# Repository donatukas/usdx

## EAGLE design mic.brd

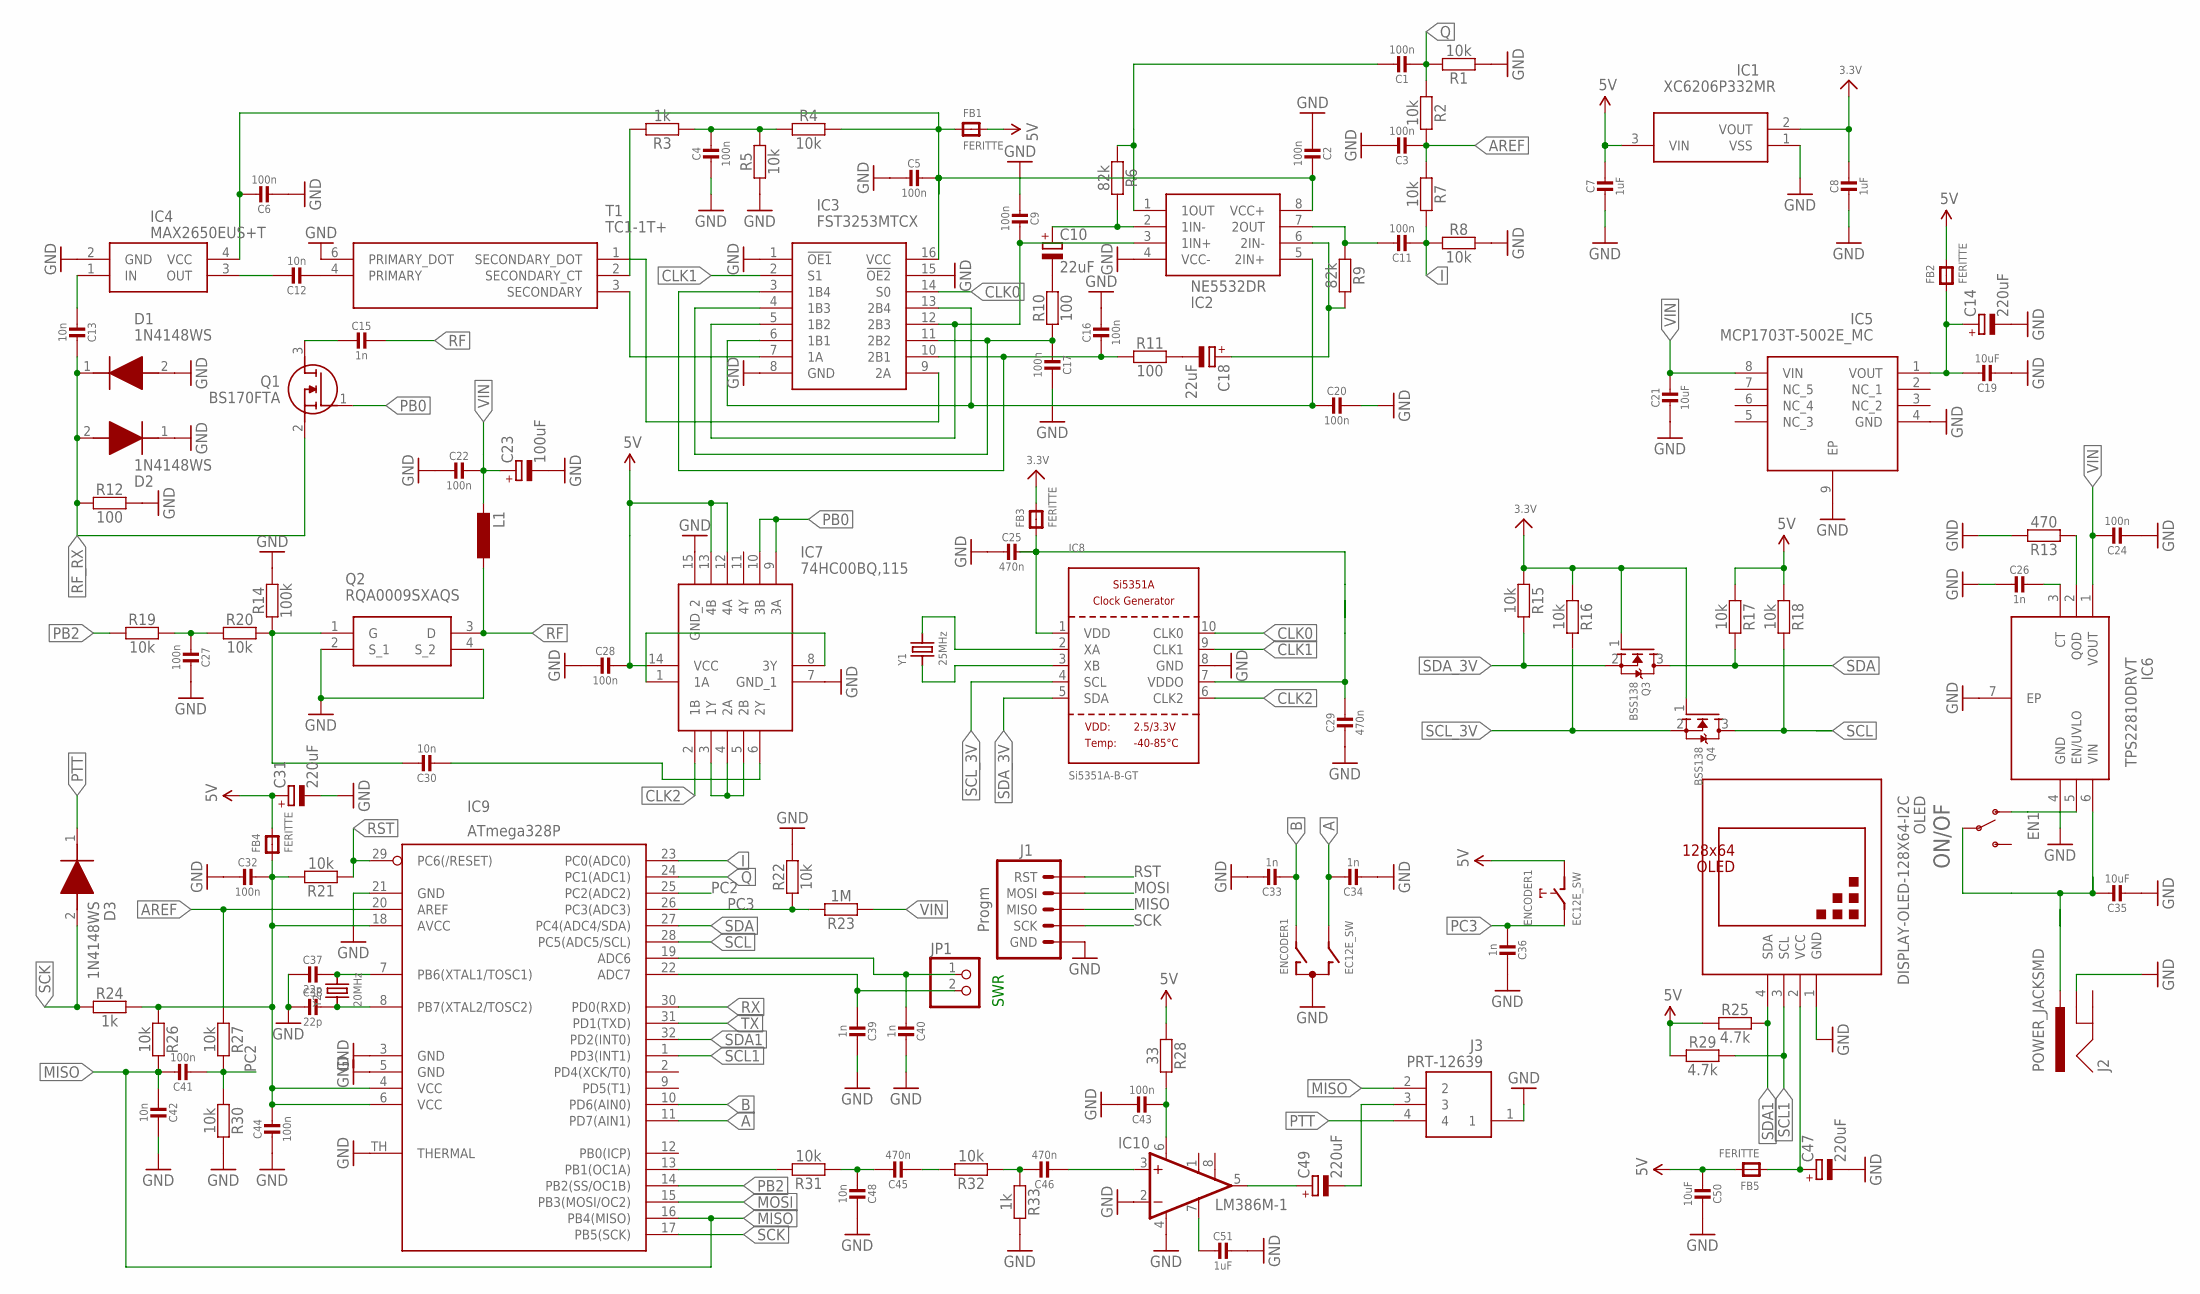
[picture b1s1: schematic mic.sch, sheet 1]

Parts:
C1, C2, C3, C4, C5, C6, C9, C11, C16, C17, C20, C22, C27, C28, C32, C41, C43, C44: 100n; _0402
C7, C8: 1uF; _0603
C10, C18: 22uF; SMC_A
C12, C13, C30, C42, C48: 10n; _0402
C14, C31, C47, C49: 220uF; SANYO-OSCON_A
C15: 1n; _0603
C19, C21, C50: 10uF; _0402
C23: 100uF; SMC_D
C24: 100n; _0805
C25, C29, C45, C46: 470n; _0402
C26, C33, C34, C36, C39, C40: 1n; _0402
C35: 10uF; _0805
C37, C38: 22p; _0402
C51: 1uF; _0402
D1: 1N4148WS; SODFL2512X90N
D2, D3: 1N4148WS; SODFL2512X90N; MANUFACTURER_PART_NUMBER 1N4148WS; MOUSER_PART_NUMBER 512-1N4148WS
ENCODER1: EC12E_SW; ALPS_EC12E_SW; MPN EC12E2424407
FB1, FB2, FB3, FB4, FB5: FERITTE; _0603
IC1: XC6206P332MR; SOT95P280X130-3N
IC2: NE5532DR; SOIC127P600X175-8N
IC3: FST3253MTCX; SOP65P640X110-16N
IC4: MAX2650EUS+T; 4-SOT143
IC5: MCP1703T-5002E_MC; SON50P300X200X100-9N
IC6: TPS22810DRVT; SON65P200X200X80-7N
IC7: 74HC00BQ,115; 74HC00BQ115
IC8: Si5351A-B-GT; MSOP10
IC9: ATmega328P; MLF32-TH
IC10: LM386M-1; SO08
J1: Progm; SPARKFUN-CONNECTORS_PIC-ICSP-MINI
J2: POWER_JACKSMD; POWER_JACK_SMD
J3: PRT-12639; PRT12639
JP1: PINHD-1X2; 1X02
L1: RCL_L-EUTFI0305; RCL_TFI0305
OLED: DISPLAY-OLED-128X64-I2C; NEW_DIY-MODULES_(1)_DISPLAY-OLED-128X64-I2C
ON/OF: SWITCH-SPDT-SMD-RIGHT-ANGLE; SWITCH_SPST_SMD_A
Q1: BS170FTA; SOT96P240X100-3N
Q2: RQA0009SXAQS
Q3, Q4: BSS138; SOT23-WIDE
R1, R2, R4, R5, R7, R8, R15, R16, R17, R18, R19, R20, R21, R22, R26, R27, R30, R31, R32: 10k; C0402
R3, R24, R33: 1k; C0402
R6, R9: 82k; C0402
R10, R11: 100; C0402
R12: 100; C0603
R13: 470; C0402
R14: 100k; C0402
R23: 1M; C0402
R25, R29: 4.7k; C0402
R28: 33; C0805
T1: TC1-1T+; TC11T
Y1: 25MHz; CRYSTAL_3.2X2.5
Y2: 20MHz; CRYSTAL_3.2X2.5

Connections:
5V: C7.1, C28.1, C31.+, C50.2, ENCODER1.D (1), FB1.2, FB2.2, FB4.2, FB5.2, IC1.3 (VIN), IC7.12 (4A), IC7.13 (4B), IC7.14 (VCC), R17.2, R18.2, R25.2, R28.2, R29.2; also elsewhere on the board
A: C34.1, ENCODER1.B, IC9.11 (PD7(AIN1))
AREF: C3.2, IC9.20 (AREF), R2.1, R7.2, R27.2
B: C33.2, ENCODER1.A, IC9.10 (PD6(AIN0))
CLK0: IC3.14 (S0), IC8.10 (CLK0)
CLK1: IC3.2 (S1), IC8.9 (CLK1)
CLK2: IC7.2 (1B), IC8.6 (CLK2)
EN1: IC6.5 (EN/UVLO), ON/OF.1 (O)
GND: C2.2, C3.1, C4.2, C5.2, C6.2, C7.2, C8.2, C9.2, C14.-, C16.1, C17.1, C19.2, C20.1, C21.2, C22.2, C23.-, C24.2, C25.2, C26.2, C27.1, C28.2, C29.2, C31.-, C32.2, C33.1, C34.2, C35.2, C36.1, C37.2, C38.2, C39.1, C40.1, C42.1, C43.1, C44.2, C47.-, C48.1, C50.1, C51.1, D1.2 (A), D2.1 (K), ENCODER1.C, IC1.1 (VSS), IC2.4 (VCC-), IC3.1 (!OE1), IC3.8 (GND), IC3.15 (!OE2), IC4.2 (GND), IC5.4 (GND), IC5.9 (EP), IC6.4 (GND), IC6.7 (EP), IC7.7 (GND_1), IC7.15 (GND_2), IC8.8 (GND), IC9.3 (GND), IC9.5 (GND), IC9.21 (GND), IC9.TH (THERMAL), IC10.2 (-IN), IC10.4 (GND), J1.5 (GND), J2.GND (GNDBREAK), J3.1, OLED.1 (GND), Q2.2 (S_1), Q2.4 (S_2), R1.2, R5.2, R8.1, R12.1, R13.2, R14.1, R22.1, R30.1, R33.1, T1.6 (PRIMARY_DOT); also elsewhere on the board
I: C11.2, IC9.23 (PC0(ADC0)), R7.1, R8.2
MISO: C41.1, C42.2, IC9.16 (PB4(MISO)), J1.3 (MISO), J3.2, R26.1
MOSI: IC9.15 (PB3(MOSI/OC2)), J1.2 (MOSI)
unnamed: IC7.3 (1Y), IC7.4 (2A), IC7.5 (2B)
unnamed: IC3.7 (1A), T1.3 (SECONDARY)
unnamed: C47.+, FB5.1, OLED.2 (VCC)
unnamed: C37.1, IC9.7 (PB6(XTAL1/TOSC1)), Y2.2
unnamed: C38.1, IC9.8 (PB7(XTAL2/TOSC2)), Y2.1
unnamed: IC3.9 (2A), T1.1 (SECONDARY_DOT)
unnamed: C4.1, R3.2, R4.2, R5.1
unnamed: IC7.1 (1A), IC7.8 (3Y)
unnamed: C30.2, IC7.6 (2Y)
unnamed: C30.1, Q2.1 (G), R14.2, R20.1
unnamed: C27.2, R19.1, R20.2
unnamed: C26.1, IC6.3 (CT)
unnamed: C20.2, IC2.5 (2IN+), IC3.6 (1B1), IC3.13 (2B4)
unnamed: C9.1, IC2.3 (1IN+), IC3.5 (1B2), IC3.12 (2B3)
unnamed: R3.1, T1.2 (SECONDARY_CT)
unnamed: C17.2, IC3.4 (1B3), IC3.11 (2B2), R10.2
unnamed: C16.2, IC3.3 (1B4), IC3.10 (2B1), R11.2
unnamed: C1.1, IC2.1 (1OUT), R6.2
unnamed: IC9.13 (PB1(OC1A)), R31.1
unnamed: C45.1, C48.2, R31.2
unnamed: C11.1, IC2.7 (2OUT), R9.2
unnamed: C18.-, R11.1
unnamed: C18.+, IC2.6 (2IN-), R9.1
unnamed: C10.+, IC2.2 (1IN-), R6.1
unnamed: C10.-, R10.1
unnamed: C45.2, R32.1
unnamed: C46.1, R32.2, R33.2
unnamed: C32.1, C44.1, FB4.1, IC9.4 (VCC), IC9.6 (VCC), IC9.18 (AVCC), R21.1, R24.1, R26.2
unnamed: C46.2, IC10.3 (+IN)
unnamed: C43.2, IC10.6 (VS), R28.1
unnamed: C51.2, IC10.7 (BYPASS)
unnamed: C49.+, IC10.5 (OUT)
unnamed: C49.-, J3.3
unnamed: C12.2, T1.4 (PRIMARY)
unnamed: C12.1, IC4.3 (OUT)
unnamed: C13.2, IC4.1 (IN)
unnamed: C15.2, Q1.3 (D)
unnamed: C14.+, C19.1, FB2.1, IC5.1 (VOUT)
unnamed: C2.1, C5.1, C6.1, FB1.1, IC2.8 (VCC+), IC3.16 (VCC), IC4.4 (VCC), R4.1
unnamed: IC8.3 (XB), Y1.1
unnamed: IC8.2 (XA), Y1.2
unnamed: IC6.2 (QOD), R13.1
unnamed: C25.1, C29.1, FB3.1, IC8.1 (VDD), IC8.7 (VDDO)
unnamed: C40.2, IC9.19 (ADC6), JP1.1
unnamed: C39.2, IC9.22 (ADC7), JP1.2
PB0: IC7.9 (3A), IC7.10 (3B), Q1.1 (G)
PB2: IC9.14 (PB2(SS/OC1B)), R19.2
PC2: C41.2, IC9.25 (PC2(ADC2)), R27.1, R30.2
PC3: C36.2, ENCODER1.E (2), IC9.26 (PC3(ADC3)), R22.2, R23.1
PTT: D3.1 (K), J3.4
Q: C1.2, IC9.24 (PC1(ADC1)), R1.1, R2.2
RF: C15.1, L1.1, Q2.3 (D); also elsewhere on the board
RF_RX: C13.1, D1.1 (K), D2.2 (A), Q1.2 (S), R12.2
RST: IC9.29 (PC6(/RESET)), J1.1 (RST), R21.2
RX: IC9.30 (PD0(RXD)); also elsewhere on the board
SCK: D3.2 (A), IC9.17 (PB5(SCK)), J1.4 (SCK), R24.2
SCL: IC9.28 (PC5(ADC5/SCL)), Q4.3 (D), R18.1; also elsewhere on the board
SCL1: IC9.1 (PD3(INT1)), OLED.3 (SCL), R29.1
SCL_3V: IC8.4 (SCL), Q4.2 (S), R16.1
SDA: IC9.27 (PC4(ADC4/SDA)), Q3.3 (D), R17.1; also elsewhere on the board
SDA1: IC9.32 (PD2(INT0)), OLED.4 (SDA), R25.1
SDA_3V: IC8.5 (SDA), Q3.2 (S), R15.1
TX: IC9.31 (PD1(TXD)); also elsewhere on the board
VDD: C8.1, FB3.2, IC1.2 (VOUT), Q3.1 (G), Q4.1 (G), R15.2, R16.2
VIN: C21.1, C22.1, C23.+, C24.1, IC5.8 (VIN), IC6.1 (VOUT), L1.2, R23.2
VIN1: C35.1, IC6.6 (VIN), J2.VIN0 (PWR), ON/OF.2

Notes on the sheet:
SWR

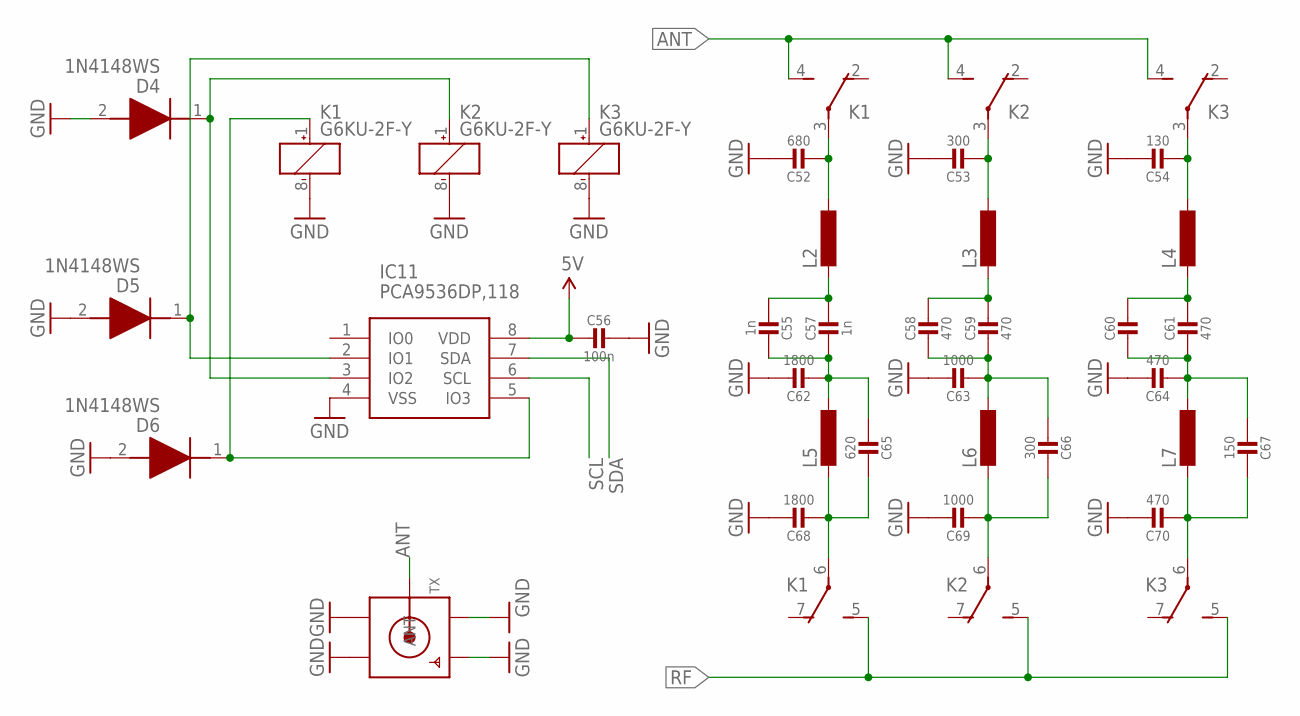
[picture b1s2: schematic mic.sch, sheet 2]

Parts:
C52: 680; _0603
C53, C66: 300; _0603
C54: 130; _0603
C55, C57: 1n; _0603
C56: 100n; _0402
C58, C59, C61, C64, C70: 470; _0603
C60: CAP_CERAMIC_0603; _0603
C62, C68: 1800; _0603
C63, C69: 1000; _0603
C65: 620; _0603
C67: 150; _0603
D4, D5: 1N4148WS; SODFL2512X90N; MANUFACTURER_PART_NUMBER 1N4148WS; MOUSER_PART_NUMBER 512-1N4148WS
D6: 1N4148WS; SODFL2512X90N
IC11: PCA9536DP,118; SOP65P490X110-8N
K1: G6KU-2F-Y
K2, K3: G6KU-2F-Y; MPN G6KU-2F-Y DC3
L2, L3, L4, L5, L6, L7: RCL_L-EUTFI0305; RCL_TFI0305
TX: MODULATOR_MICROBUILDER_SMACONNECTOR_EDGE_UFL; MODULATOR_MICROBUILDER_SMA_EDGELAUNCH_UFL

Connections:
5V: C56.2, IC11.8 (VDD); also elsewhere on the board
ANT: K1.4 (S), K2.4 (S), K3.4 (S), TX.P (ANT)
GND: C52.1, C53.1, C54.1, C56.1, C62.1, C63.1, C64.1, C68.1, C69.1, C70.1, D4.2 (A), D5.2 (A), D6.2 (A), IC11.4 (VSS), K1.8 (-), K2.8 (-), K3.8 (-), TX.GND@1 (GND1), TX.GND@2 (GND2), TX.GND@3 (GND3), TX.GND@4 (GND4); also elsewhere on the board
unnamed: C55.2, C57.1, L2.2
unnamed: C55.1, C57.2, C62.2, C65.2, L5.1
unnamed: C58.1, C59.1, L3.2
unnamed: C52.2, K1.3, L2.1
unnamed: C53.2, K2.3, L3.1
unnamed: C54.2, K3.3, L4.1
unnamed: C67.1, C70.2, K3.6, L7.2
unnamed: C66.1, C69.2, K2.6, L6.2
unnamed: C65.1, C68.2, K1.6, L5.2
unnamed: C58.2, C59.2, C63.2, C66.2, L6.1
unnamed: C60.2, C61.2, C64.2, C67.2, L7.1
unnamed: C60.1, C61.1, L4.2
unnamed: D6.1 (K), IC11.5 (IO3), K1.1 (+)
unnamed: D4.1 (K), IC11.3 (IO2), K2.1 (+)
unnamed: D5.1 (K), IC11.2 (IO1), K3.1 (+)
RF: K1.5 (S), K2.5 (S), K3.5 (S); also elsewhere on the board
SCL: IC11.6 (SCL); also elsewhere on the board
SDA: IC11.7 (SDA); also elsewhere on the board

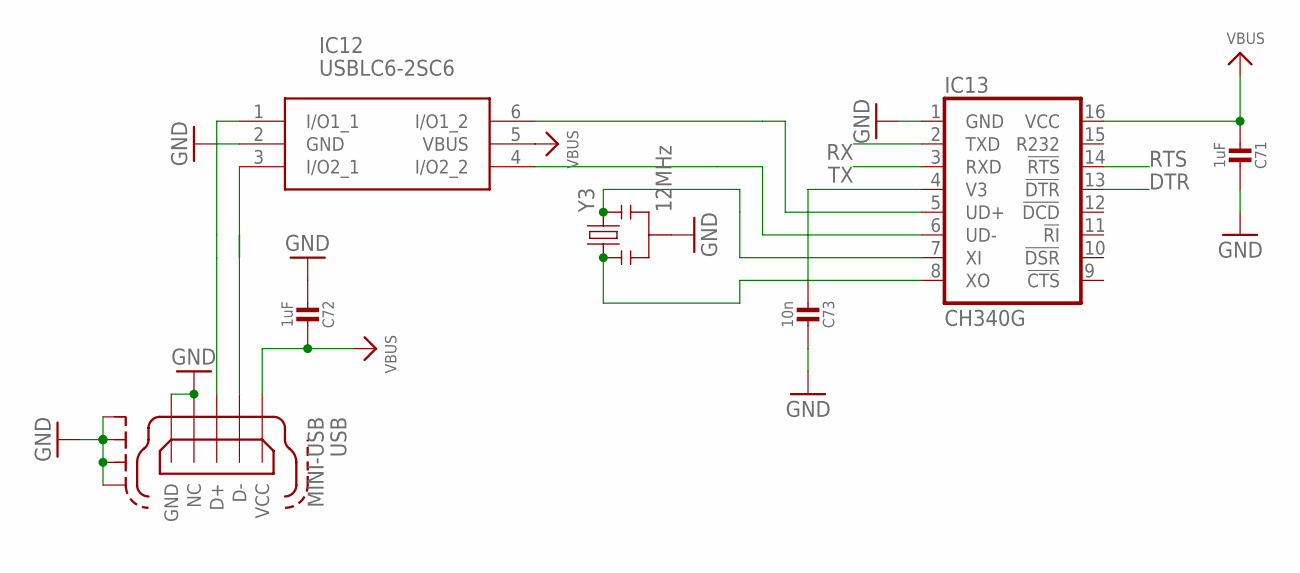
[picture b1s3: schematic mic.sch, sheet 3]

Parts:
C71, C72: 1uF; _0603
C73: 10n; _0603
IC12: USBLC6-2SC6; SOT95P280X145-6N
IC13: CH340G; SO016
USB: MINI-USB; MINI-USB-B5
Y3: 12MHz; RESONATOR-SMD

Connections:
DTR: IC13.13 (!DTR)
GND: C71.1, C72.2, C73.1, IC12.2 (GND), IC13.1 (GND), USB.4 (NC), USB.5 (GND), USB.M1 (S1), USB.M2 (S2), USB.M3 (S3), USB.M4 (S4), Y3.2; also elsewhere on the board
unnamed: IC12.6 (I/O1_2), IC13.5 (UD+)
unnamed: IC12.4 (I/O2_2), IC13.6 (UD-)
unnamed: IC13.8 (XO), Y3.1
unnamed: IC13.7 (XI), Y3.3
unnamed: IC12.1 (I/O1_1), USB.3 (D+)
unnamed: IC12.3 (I/O2_1), USB.2 (D-)
RTS: IC13.14 (!RTS)
RX: IC13.2 (TXD); also elsewhere on the board
TX: IC13.3 (RXD); also elsewhere on the board
V3: C73.2, IC13.4 (V3)
VBUS: C71.2, C72.1, IC12.5 (VBUS), IC13.16 (VCC), USB.1 (VCC)

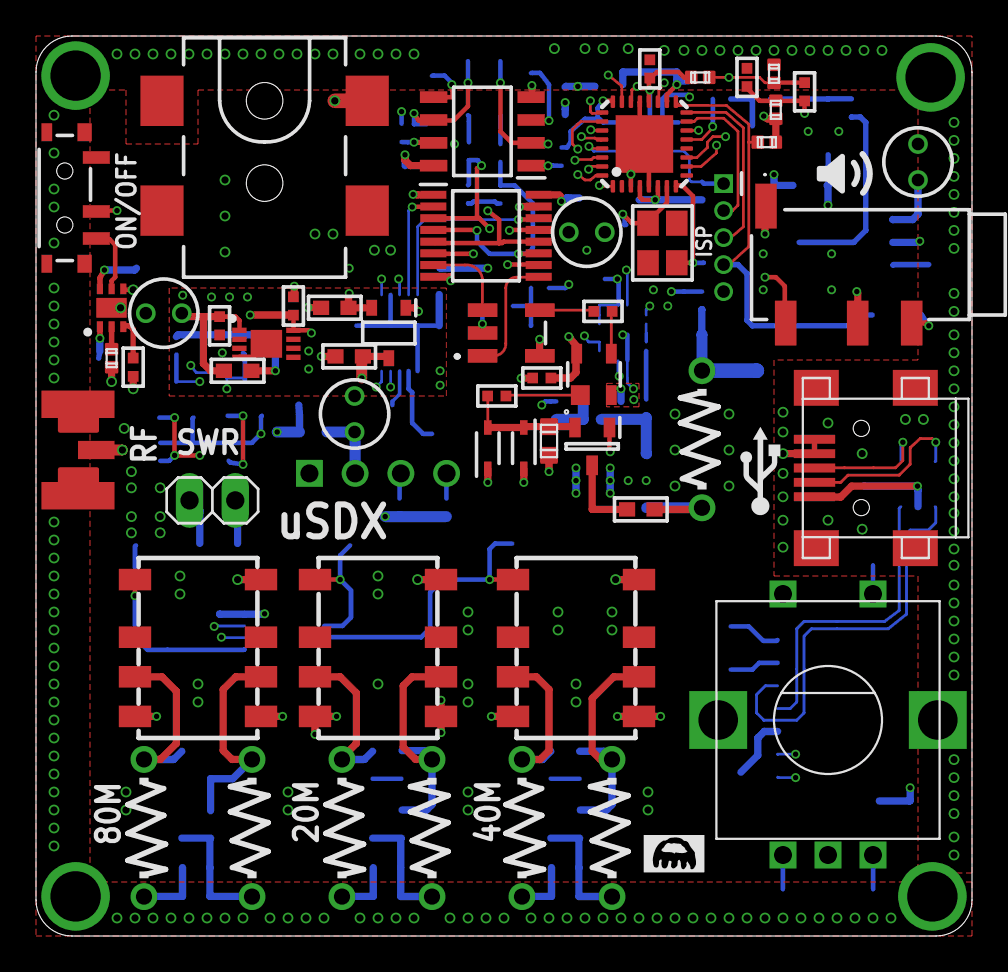
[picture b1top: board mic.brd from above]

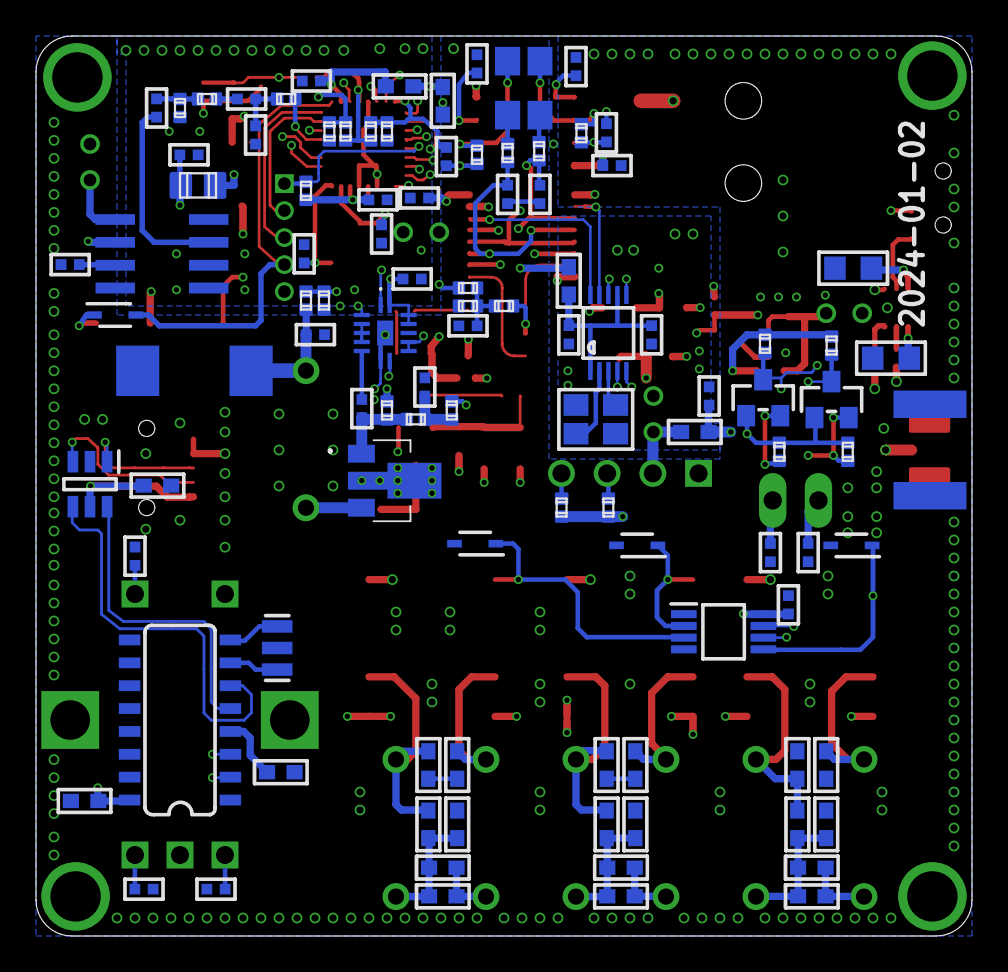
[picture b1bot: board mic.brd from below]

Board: 6 copper layers, 52.0 x 50.0 mm, 157 parts (103 on the bottom side), 102 nets.

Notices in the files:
parts and their libraries:
microbuilder: This work is placed in the public domain, and may be freely used for commercial and non-commercial work with the following conditions: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
SparkFun-Connectors: Licensing: Creative Commons ShareAlike 4.0 International - https://creativecommons.org/licenses/by-sa/4.0
